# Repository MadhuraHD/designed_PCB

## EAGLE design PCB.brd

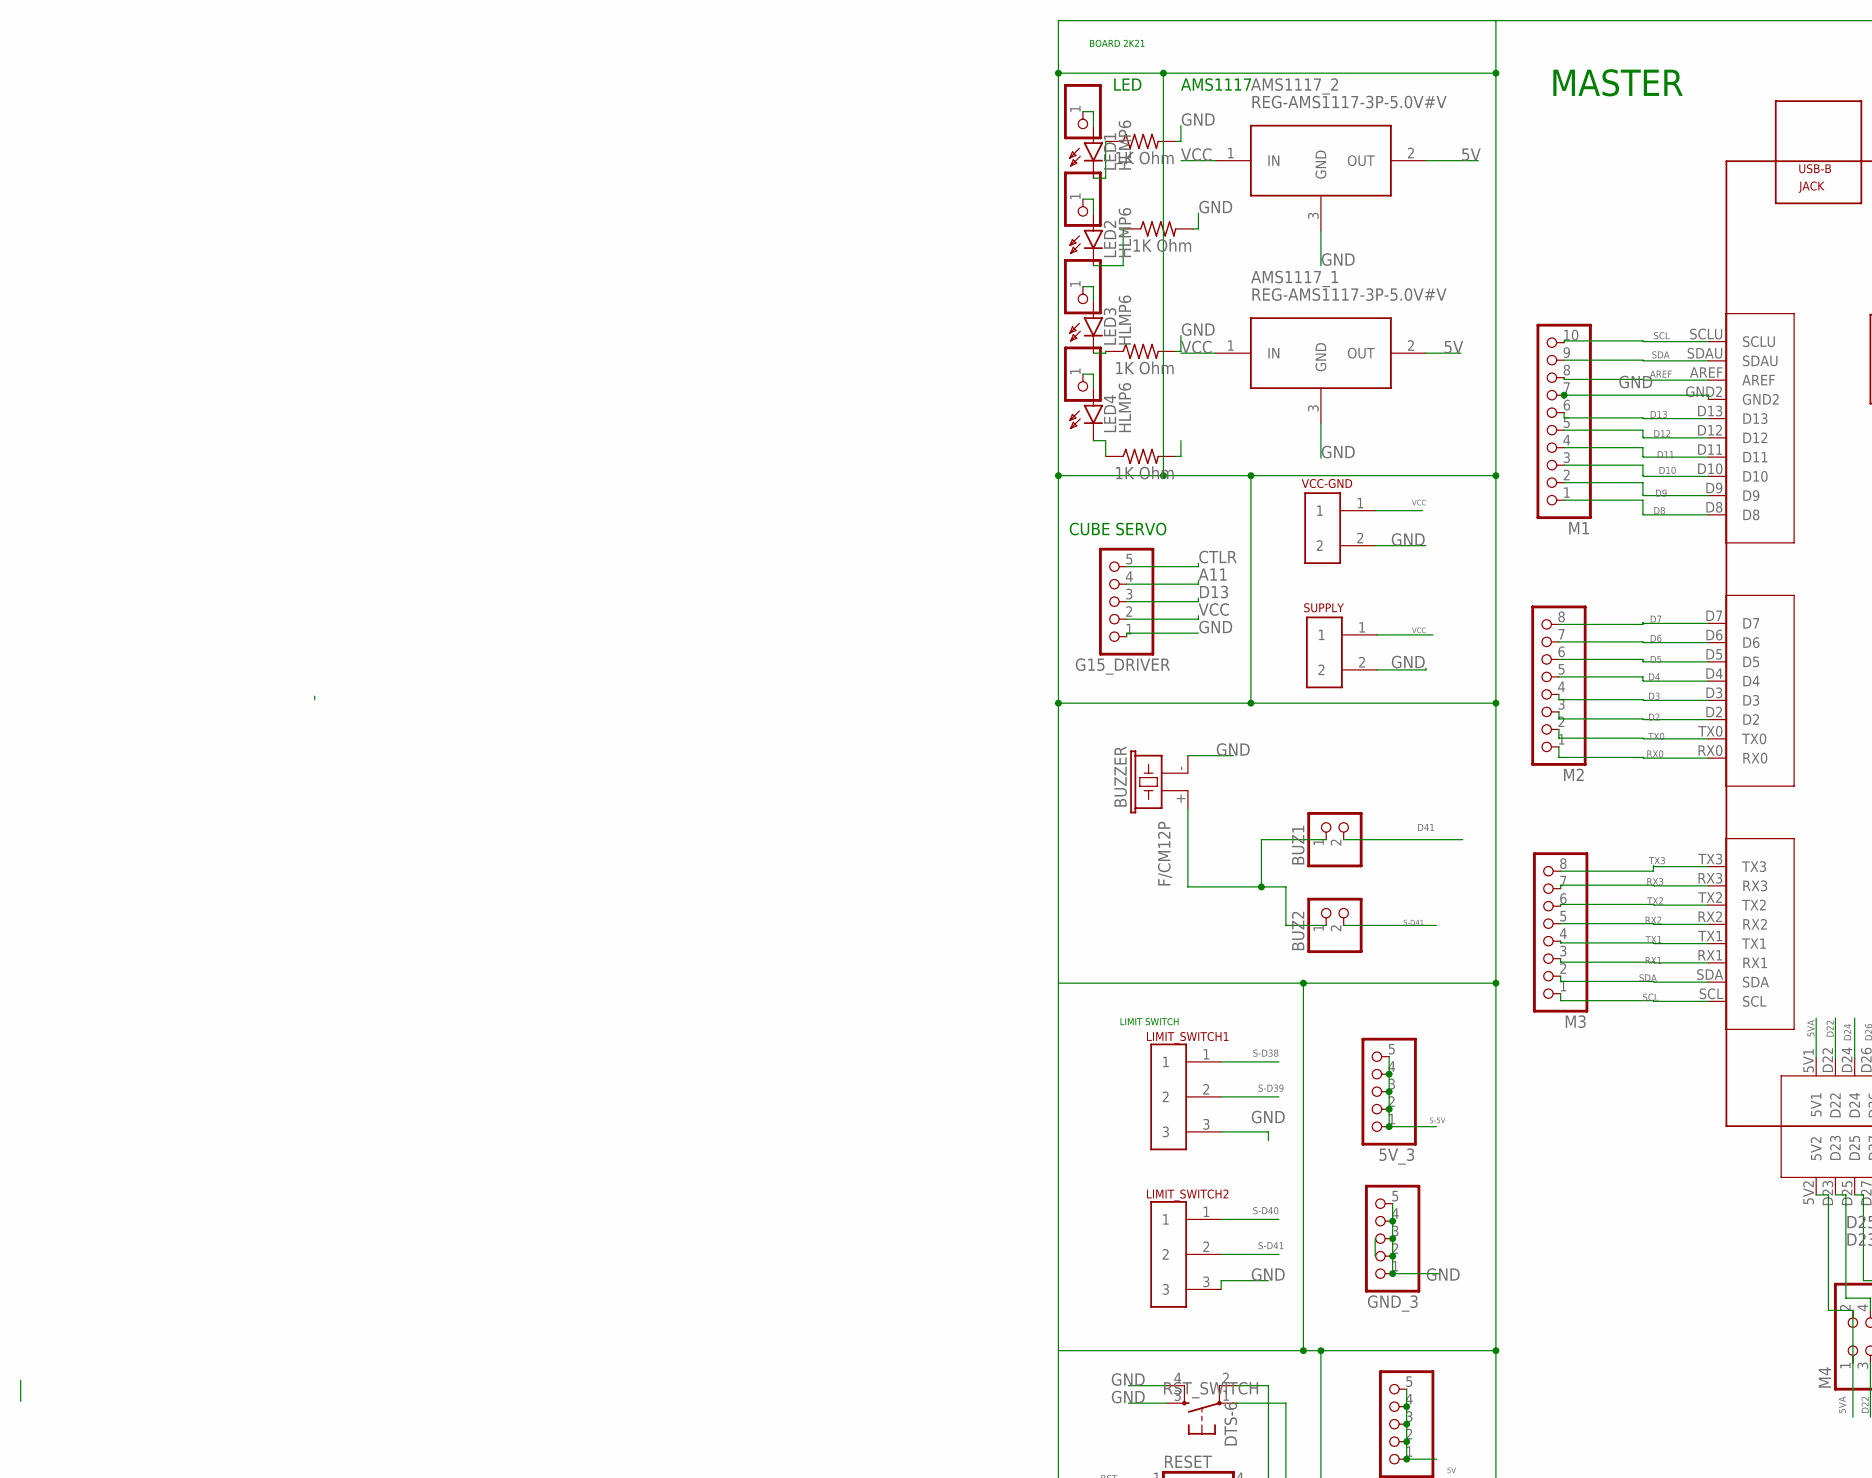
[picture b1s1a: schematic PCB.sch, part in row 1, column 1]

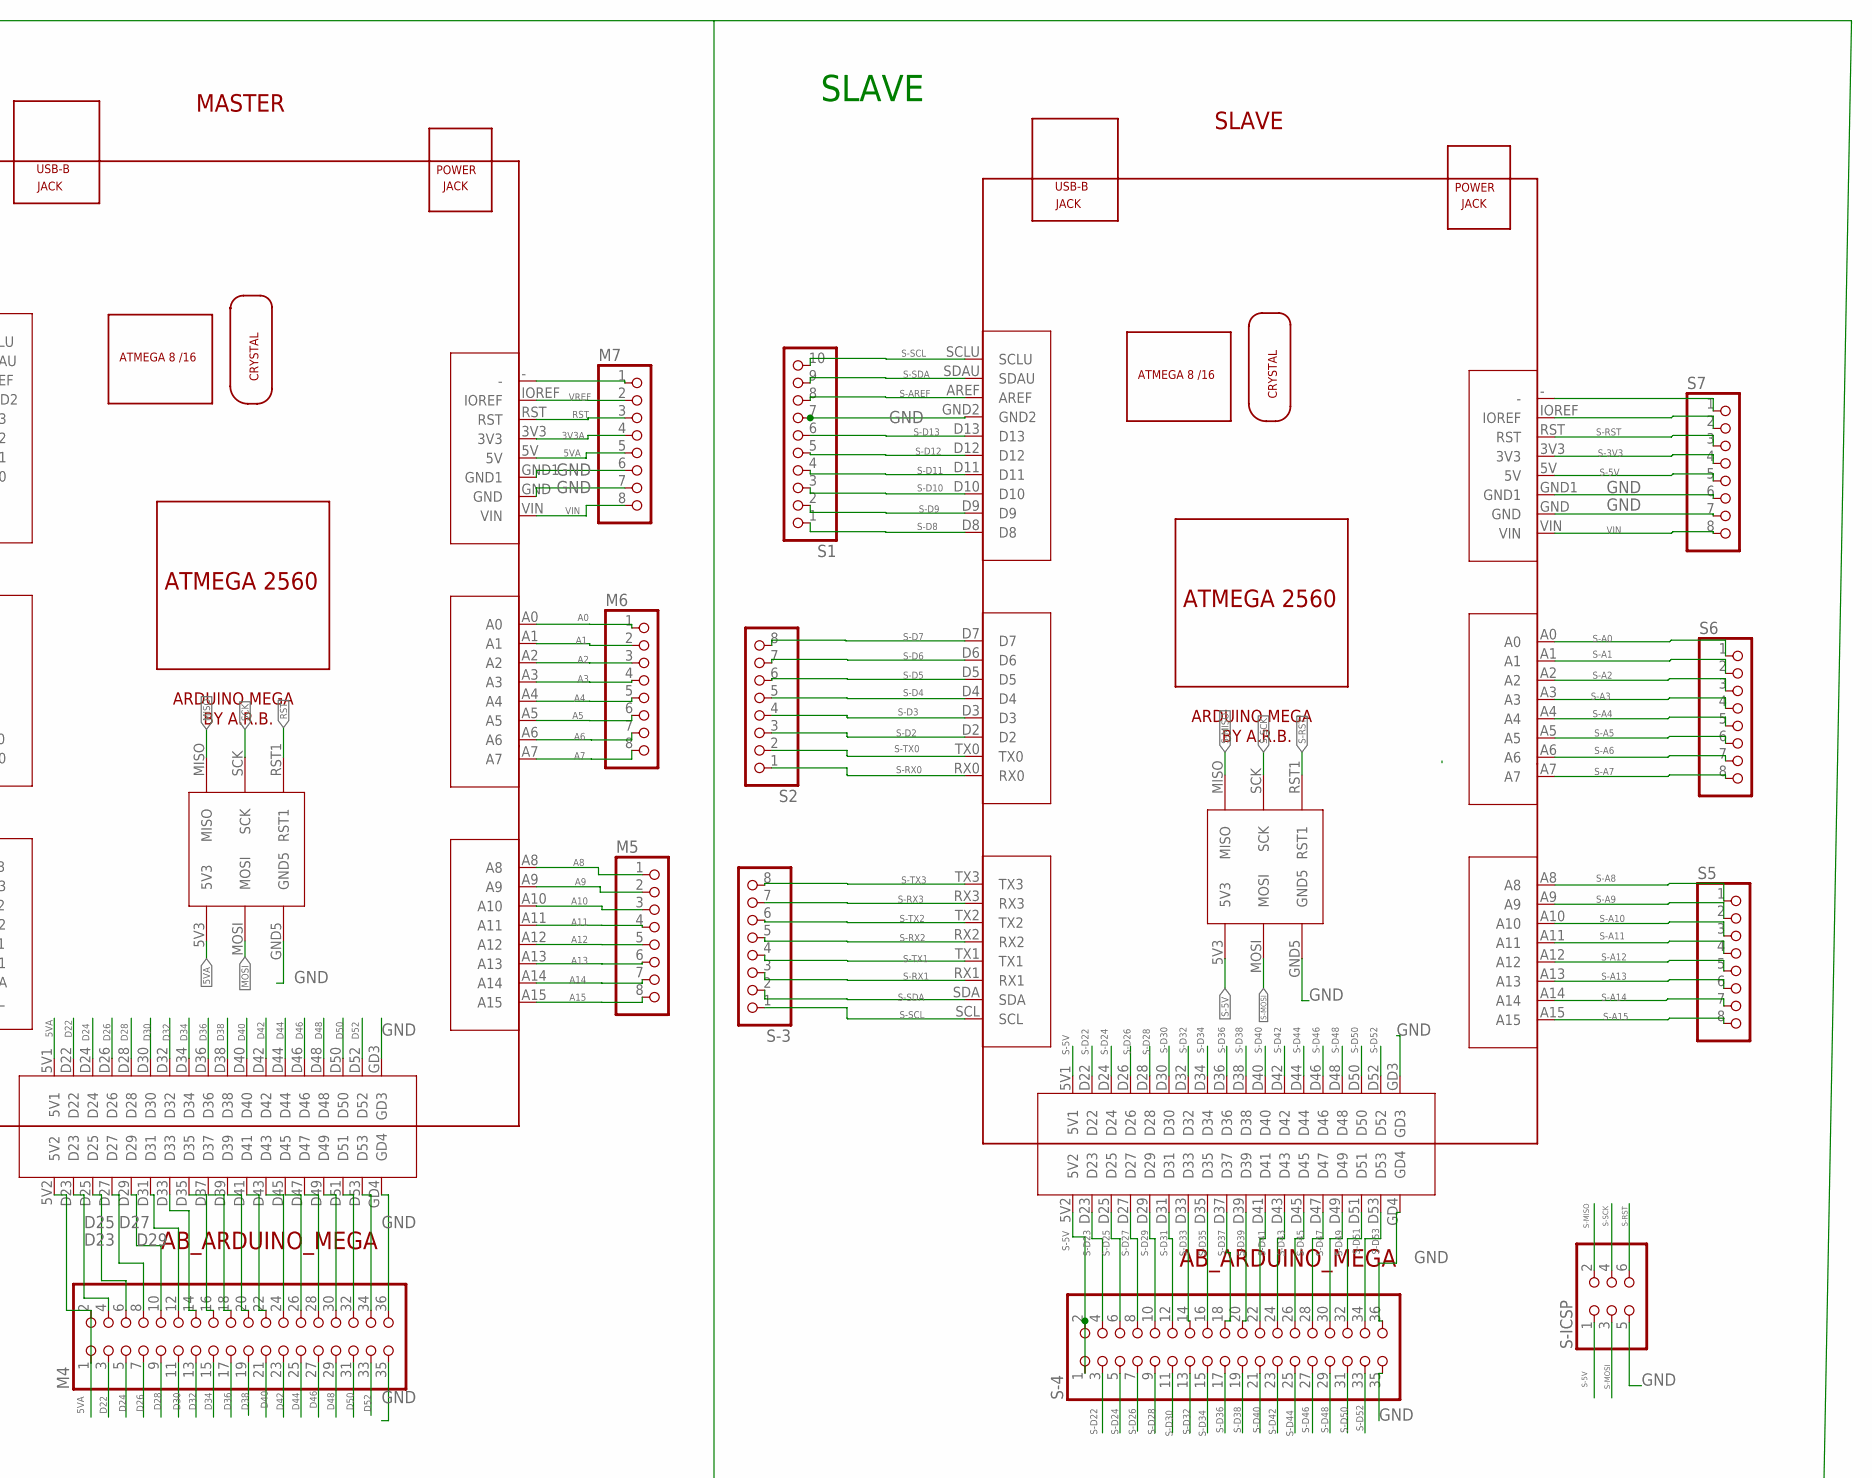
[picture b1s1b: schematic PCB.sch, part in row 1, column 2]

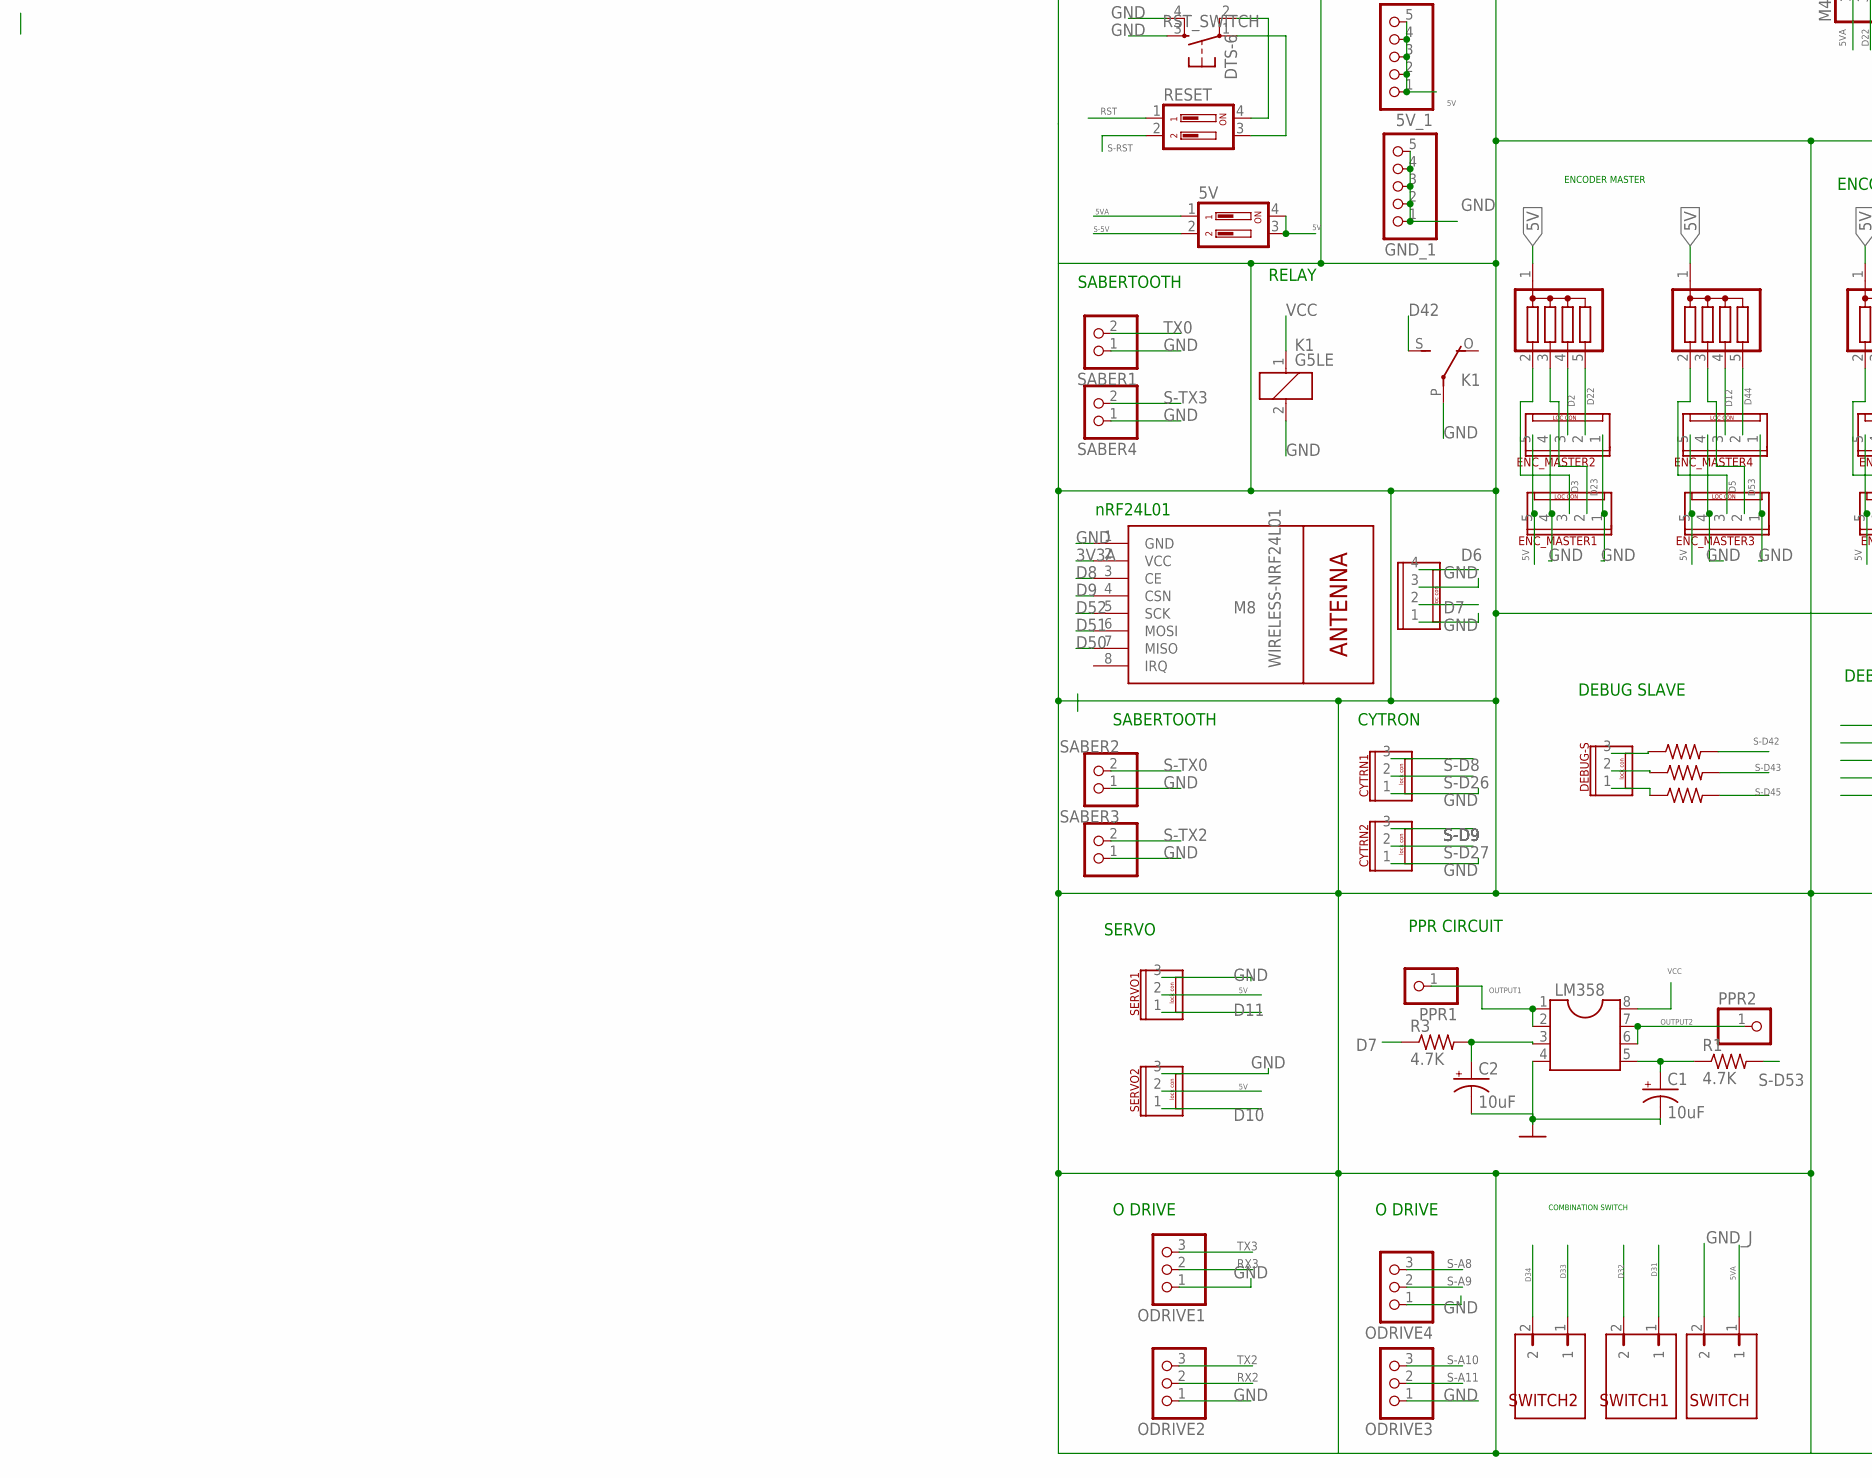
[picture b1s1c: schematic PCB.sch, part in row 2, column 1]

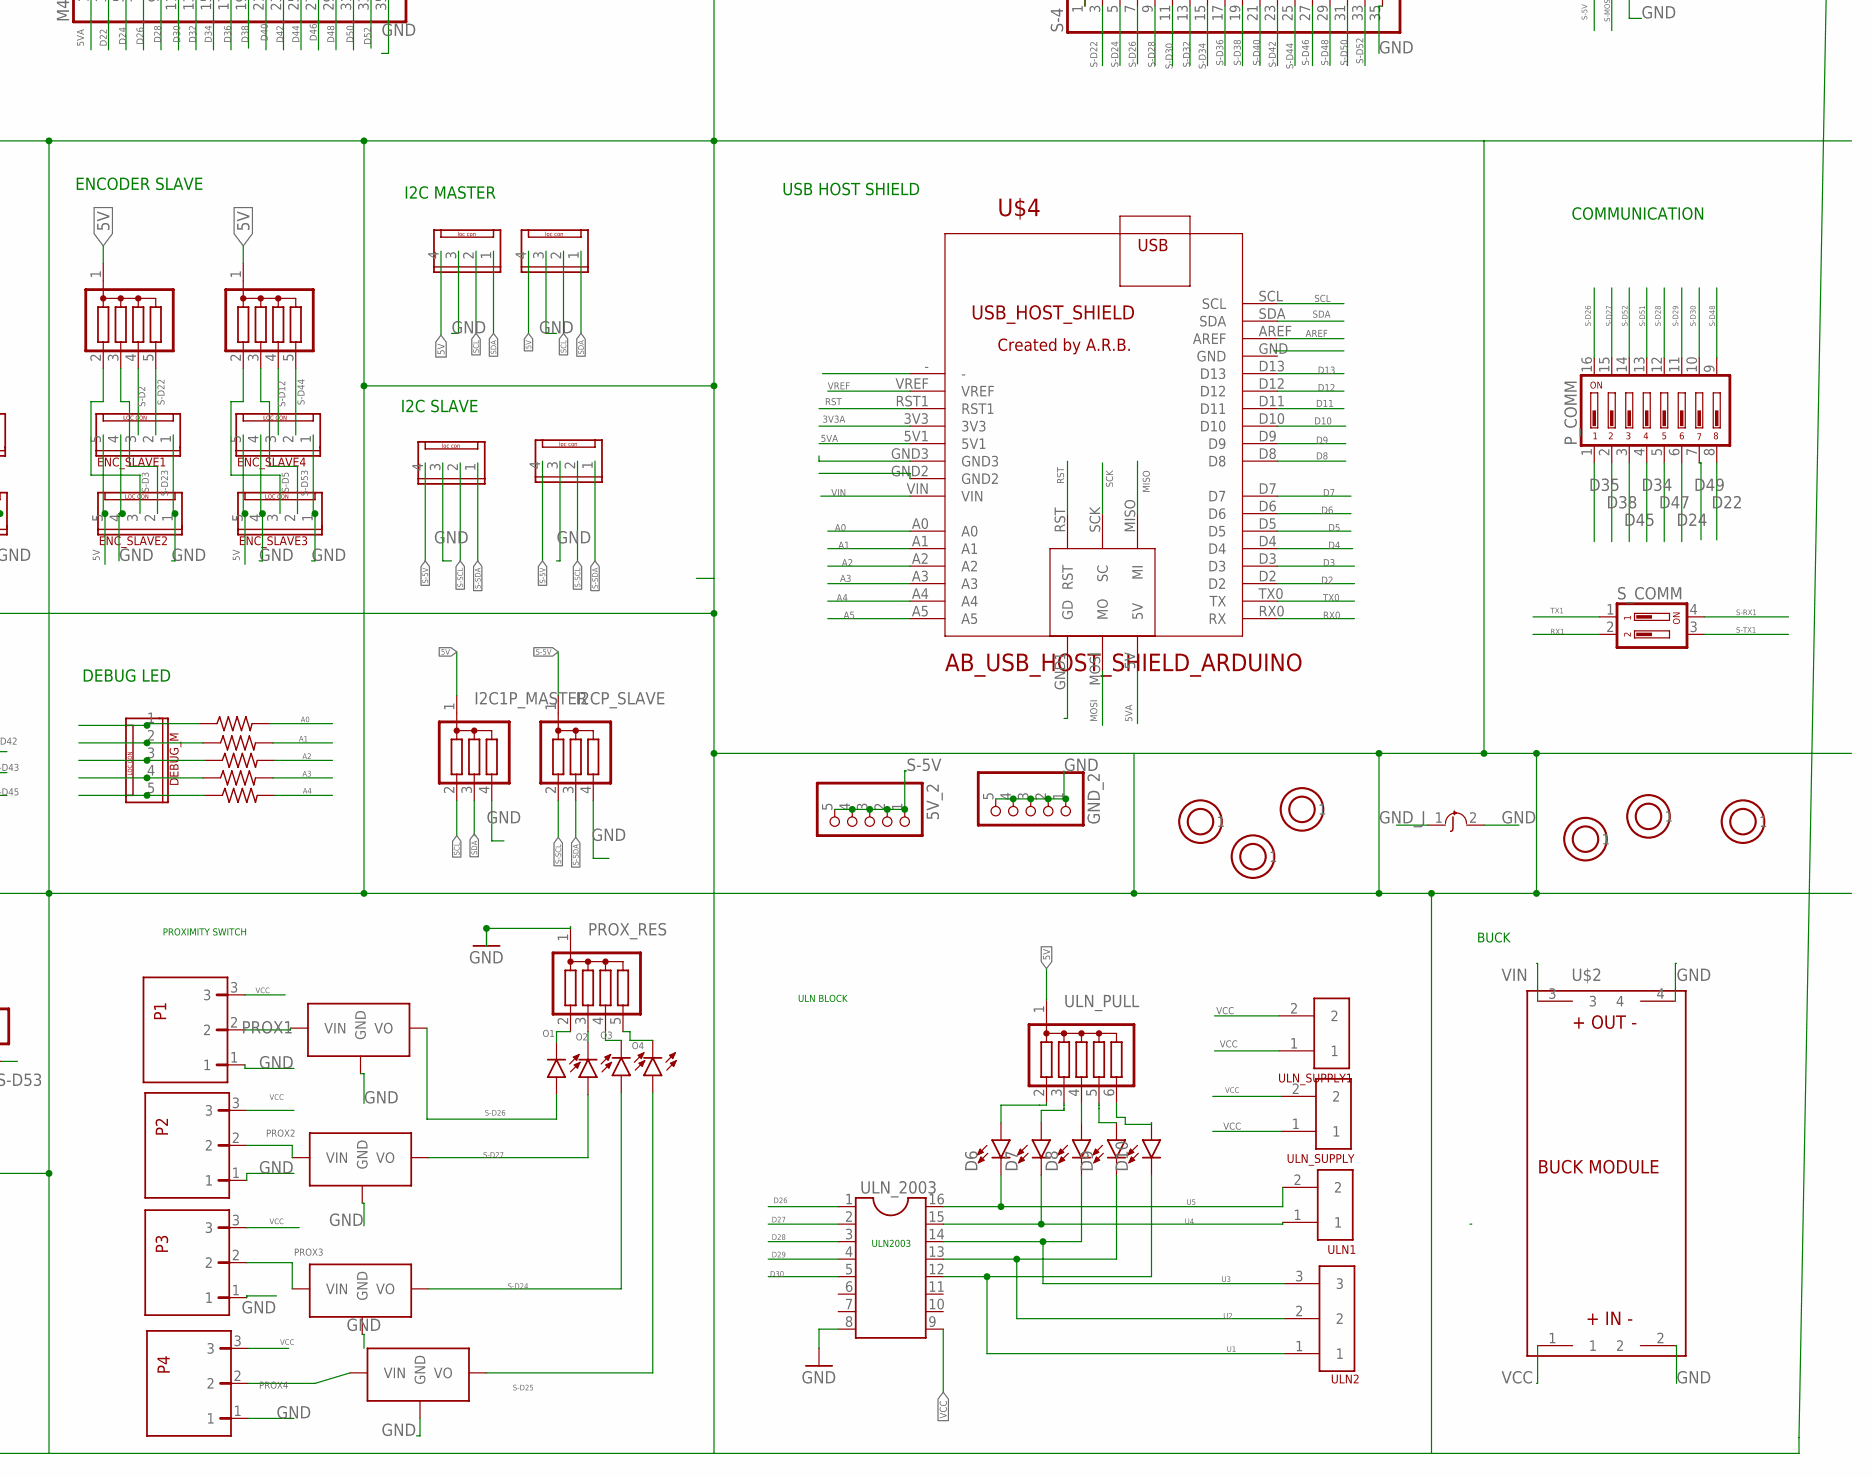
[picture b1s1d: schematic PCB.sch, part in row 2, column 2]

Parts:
5V: DIP02YL
5V_1, 5V_2, 5V_3: PINHD-1X5; 1X05
AMS1117_1, AMS1117_2: REG-AMS1117-3P-5.0V#V; REG-AMS1117-3P#V
BUZ1, BUZ2: PINHD-1X2; 1X02
BUZZER: F/CM12P
C1, C2: 10uF; CPOL-RADIAL-2.5MM-5MM
CYTRN1, CYTRN2: AB_3PIN_LOC_CONNECTOR
D1, D2, D3, D6, D7, D8, D9, D10, D14: LED-3MM-NO_SILK; LED_3MM-NS
DEBUG-S: AB_3PIN_LOC_CONNECTOR
DEBUG_M: AB_5PIN_LOC_CONNECTOR
ENC_MASTER1, ENC_MASTER2, ENC_MASTER3, ENC_MASTER4: AB_5PIN_LOC_CONNECTOR
ENC_SLAVE1, ENC_SLAVE2, ENC_SLAVE3, ENC_SLAVE4: AB_5PIN_LOC_CONNECTOR
G15_DRIVER: PINHD-1X5; 1X05
GND_1, GND_2, GND_3: PINHD-1X5; 1X05
I2C1P_MASTER, I2CP_SLAVE: G03R; SIL4
IMU_BLOCK2, IMU_BLOCK3, IMU_BLOCK4: AB_4PIN_LOC_CONNECTOR
IMU_MASTER: AB_4PIN_LOC_CONNECTOR
K1: G5LE
LED1, LED2, LED3, LED4: HLMP6
LIMIT_SWITCH1, LIMIT_SWITCH2: AB_SCREW_TER_5MM_3PIN
LM358: DIL8; DIL08
M1: PINHD-1X10; 1X10
M2, M3, M5, M6, M7: PINHD-1X8; 1X08
M4: PINHD-2X18; 2X18
M8: WIRELESS-NRF24L01
MASTER: AB_ARDUINO_MEGA
ODRIVE1, ODRIVE2, ODRIVE3, ODRIVE4: PINHD-1X3; 1X03
P1: P1; AB_RIGHT_TER_BLK_3PIN
P2: P2; AB_RIGHT_TER_BLK_3PIN
P3: P3; AB_RIGHT_TER_BLK_3PIN
P4: P4; AB_RIGHT_TER_BLK_3PIN
PPR1, PPR2, PPR5, PPR6, PPR7, PPR8: PINHD-1X1; 1X01
PROX_RES: G04R; SIL5
PULL_MASTER1, PULL_MASTER2: G04R; SIL5
PULL_SLAVE3: G04R; SIL5
P_COMM: DIP08YL
R1, R3: 4.7K; 0204/7
R2, R4, R5, R6, R7, R8, R9, R10: R-US_0204/7; 0204/7
R13, R14, R15, R16: 1K Ohm; 0204/7
RESET: DIP02YL
RST_SWITCH: DTS-6
S1: PINHD-1X10; 1X10
S2, S5, S6, S7: PINHD-1X8; 1X08
S-3: PINHD-1X8; 1X08
S-4: PINHD-2X18; 2X18
S-ICSP: PINHD-2X3; 2X03
SABER1, SABER2, SABER3, SABER4: PINHD-1X2; 1X02
SERVO1, SERVO2: AB_3PIN_LOC_CONNECTOR
SLAVE: AB_ARDUINO_MEGA
STEPPER: AB_4PIN_LOC_CONNECTOR
SUPPLY: AB_SCREW_TERMINAL_5MM_2PIN
SWITCH, SWITCH1, SWITCH2: AB_RIGHT_TER_BLK
S_COMM: DIP02YL
S_ENC_PULL1: G04R; SIL5
U$2: BUCK_MODULEWITH_SMDPADS&THROUGHHOLES; BUCK_MODULE
U$3, U$5, U$6, U$7, U$8, U$9: PLATED_DRILL_3.5MM
U$4: AB_USB_HOST_SHIELD_ARDUINO
U$23, U$24, U$25, U$26: AB_7805_FLAT
U$35: AB_JUMPER_ONE_WAY
ULN1: AB_SCREW_TERMINAL_5MM_2PIN
ULN2: AB_SCREW_TER_5MM_3PIN
ULN_2003: DIL16
ULN_PULL: G05R; SIL6
ULN_SUPPLY, ULN_SUPPLY1: AB_SCREW_TERMINAL_5MM_2PIN
VCC-GND: AB_SCREW_TERMINAL_5MM_2PIN

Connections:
3V3A: M7.4, M8.2 (VCC), MASTER.3V3, U$4.3V3
5V: 5V.3, 5V.4, 5V_1.1, 5V_1.2, 5V_1.3, 5V_1.4, 5V_1.5, AMS1117_1.2 (OUT), AMS1117_2.2 (OUT), ENC_MASTER1.5, ENC_MASTER2.5, ENC_MASTER3.5, ENC_MASTER4.5, ENC_SLAVE1.5, ENC_SLAVE2.5, ENC_SLAVE3.5, ENC_SLAVE4.5, I2C1P_MASTER.1, IMU_BLOCK2.4, IMU_MASTER.4, PULL_MASTER1.1, PULL_MASTER2.1, PULL_SLAVE3.1, SERVO1.2, SERVO2.2, S_ENC_PULL1.1, ULN_PULL.1
5VA: 5V.1, M4.1, M4.2, M7.5, MASTER.5V, MASTER.5V1, MASTER.5V2, MASTER.5V3, SWITCH.1, U$4.5V, U$4.5V1
A0: M6.1, MASTER.A0, R2.2, U$4.A0
A1: M6.2, MASTER.A1, R4.2, U$4.A1
A2: M6.3, MASTER.A2, R5.2, U$4.A2
A3: M6.4, MASTER.A3, R6.2, U$4.A3
A4: M6.5, MASTER.A4, R7.2, U$4.A4
A5: M6.6, MASTER.A5, U$4.A5
A6: M6.7, MASTER.A6
A7: M6.8, MASTER.A7
A8: M5.1, MASTER.A8
A9: M5.2, MASTER.A9
A10: M5.3, MASTER.A10
A11: G15_DRIVER.4, M5.4, MASTER.A11
A12: M5.5, MASTER.A12
A13: M5.6, MASTER.A13
A14: M5.7, MASTER.A14
A15: M5.8, MASTER.A15
AREF: M1.8, MASTER.AREF, U$4.AREF
CTLR: G15_DRIVER.5
D2: ENC_MASTER2.3, M2.3, MASTER.D2, PULL_MASTER1.4, U$4.D2
D3: ENC_MASTER1.3, M2.4, MASTER.D3, PULL_MASTER1.2, U$4.D3
D4: M2.5, MASTER.D4, U$4.D4
D5: ENC_MASTER3.3, M2.6, MASTER.D5, PULL_MASTER2.2, U$4.D5
D6: M2.7, MASTER.D6, STEPPER.4, U$4.D6
D7: M2.8, MASTER.D7, R3.1, STEPPER.2, U$4.D7
D8: M1.1, M8.3 (CE), MASTER.D8, U$4.D8
D9: M1.2, M8.4 (CSN), MASTER.D9, U$4.D9
D10: M1.3, MASTER.D10, SERVO2.1, U$4.D10
D11: M1.4, MASTER.D11, SERVO1.1, U$4.D11
D12: ENC_MASTER4.3, M1.5, MASTER.D12, PULL_MASTER2.4, U$4.D12
D13: G15_DRIVER.3, M1.6, MASTER.D13, U$4.D13
D22: ENC_MASTER2.2, M4.3, MASTER.D22, PULL_MASTER1.5, P_COMM.8
D23: ENC_MASTER1.2, M4.4, MASTER.D23, PULL_MASTER1.3
D24: M4.5, MASTER.D24, P_COMM.6
D25: M4.6, MASTER.D25
D26: M4.7, MASTER.D26, ULN_2003.1
D27: M4.8, MASTER.D27, ULN_2003.2
D28: M4.9, MASTER.D28, ULN_2003.3
D29: M4.10, MASTER.D29, ULN_2003.4
D30: M4.11, MASTER.D30, ULN_2003.5
D31: M4.12, MASTER.D31, SWITCH1.1
D32: M4.13, MASTER.D32, SWITCH1.2
D33: M4.14, MASTER.D33, SWITCH2.1
D34: M4.15, MASTER.D34, P_COMM.4, SWITCH2.2
D35: M4.16, MASTER.D35, P_COMM.1
D36: M4.17, MASTER.D36
D38: M4.19, MASTER.D38, P_COMM.2
D39: M4.18, MASTER.D37
D40: M4.21, MASTER.D40
D41: BUZ1.2, M4.20, MASTER.D39
D42: K1.S, M4.23, MASTER.D42
D43: M4.22, MASTER.D41
D44: ENC_MASTER4.2, M4.25, MASTER.D44, PULL_MASTER2.5
D45: M4.24, MASTER.D43, P_COMM.3
D46: M4.27, MASTER.D46
D47: M4.26, MASTER.D45, P_COMM.5
D48: M4.29, MASTER.D48
D49: M4.28, MASTER.D47, P_COMM.7
D50: M4.31, M8.7 (MISO), MASTER.D50
D51: M4.30, M8.6 (MOSI), MASTER.D49
D52: M4.33, M8.5 (SCK), MASTER.D52
D53: ENC_MASTER3.2, M4.32, MASTER.D51, PULL_MASTER2.3
D54: M4.34, MASTER.D53
GND: AMS1117_1.3 (GND), AMS1117_2.3 (GND), BUZZER.- (2), C1.2 (-), C2.2 (-), CYTRN1.1, CYTRN2.1, ENC_MASTER1.1, ENC_MASTER1.4, ENC_MASTER2.1, ENC_MASTER2.4, ENC_MASTER3.1, ENC_MASTER3.4, ENC_MASTER4.1, ENC_MASTER4.4, ENC_SLAVE1.1, ENC_SLAVE1.4, ENC_SLAVE2.1, ENC_SLAVE2.4, ENC_SLAVE3.1, ENC_SLAVE3.4, ENC_SLAVE4.1, ENC_SLAVE4.4, G15_DRIVER.1, GND_1.1, GND_1.2, GND_1.3, GND_1.4, GND_1.5, GND_2.1, GND_2.2, GND_2.3, GND_2.4, GND_2.5, GND_3.1, GND_3.2, GND_3.3, GND_3.4, GND_3.5, I2C1P_MASTER.4, I2CP_SLAVE.4, IMU_BLOCK2.3, IMU_BLOCK3.3, IMU_BLOCK4.3, IMU_MASTER.3, K1.2, K1.P, LIMIT_SWITCH1.3, LIMIT_SWITCH2.3, LM358.4, M1.7, M4.35, M4.36, M7.6, M7.7, M8.1 (GND), MASTER.GD3, MASTER.GD4, MASTER.GND, MASTER.GND1, MASTER.GND2, MASTER.GND5, ODRIVE1.1, ODRIVE2.1, ODRIVE3.1, ODRIVE4.1, P1.1, P2.1, P3.1, P4.1, PROX_RES.1, R13.2, R14.2, R15.2, RST_SWITCH.3, RST_SWITCH.4, S1.7, S7.6, S7.7, S-4.35, S-4.36, S-ICSP.5, SABER1.1, SABER2.1, SABER3.1, SABER4.1, SERVO1.3, SERVO2.3, SLAVE.GD3, SLAVE.GD4, SLAVE.GND, SLAVE.GND1, SLAVE.GND2, SLAVE.GND5, STEPPER.1, STEPPER.3, SUPPLY.2, U$2.2, U$2.4, U$23.2 (GND), U$24.2 (GND), U$25.2 (GND), U$26.2 (GND), U$35.2, ULN_2003.8, VCC-GND.2
GND_J: SWITCH.2, U$35.1
MISO: MASTER.MISO, U$4.MISO (MI)
MOSI: MASTER.MOSI, U$4.MOSI (MO)
unnamed: C1.1 (+), LM358.5, R1.1
unnamed: M7.1, MASTER.-
unnamed: S7.1, SLAVE.-
unnamed: BUZ1.1, BUZ2.1, BUZZER.+ (1)
unnamed: C2.1 (+), LM358.3, R3.2
unnamed: DEBUG_M.1, R2.1
unnamed: D6.A, ULN_PULL.2
unnamed: D7.A, ULN_PULL.3
unnamed: D8.A, ULN_PULL.4
unnamed: D9.A, ULN_PULL.5
unnamed: D10.A, ULN_PULL.6
unnamed: RESET.4, RST_SWITCH.2
unnamed: RESET.3, RST_SWITCH.1
unnamed: DEBUG_M.2, R4.1
unnamed: DEBUG_M.3, R5.1
unnamed: DEBUG_M.4, R6.1
unnamed: DEBUG_M.5, R7.1
unnamed: LED1.A, PPR5.1
unnamed: LED2.A, PPR6.1
unnamed: DEBUG-S.3, R8.1
unnamed: DEBUG-S.2, R9.1
unnamed: DEBUG-S.1, R10.1
unnamed: LED3.A, PPR7.1
unnamed: LED4.A, PPR8.1
unnamed: LED4.K, R16.1
unnamed: LED3.K, R15.1
unnamed: LED2.K, R14.1
unnamed: LED1.K, R13.1
unnamed: S7.2, SLAVE.IOREF
O1: D14.K (C), PROX_RES.2
O2: D1.K (C), PROX_RES.3
O3: D2.K (C), PROX_RES.4
O4: D3.K (C), PROX_RES.5
OUTPUT1: LM358.1, LM358.2, PPR1.1
OUTPUT2: LM358.6, LM358.7, PPR2.1
PROX1: P1.2, U$23.1 (VIN)
PROX2: P2.2, U$24.1 (VIN)
PROX3: P3.2, U$25.1 (VIN)
PROX4: P4.2, U$26.1 (VIN)
RST: M7.3, MASTER.RST, MASTER.RST1, RESET.1, U$4.RST, U$4.RST1
RX0: M2.1, MASTER.RX0, U$4.RX0 (RX)
RX1: M3.3, MASTER.RX1, S_COMM.2
RX2: M3.5, MASTER.RX2, ODRIVE2.2
RX3: M3.7, MASTER.RX3, ODRIVE1.2
S-3V3: S7.4, SLAVE.3V3
S-5V: 5V.2, 5V_2.1, 5V_2.2, 5V_2.3, 5V_2.4, 5V_2.5, 5V_3.1, 5V_3.2, 5V_3.3, 5V_3.4, 5V_3.5, I2CP_SLAVE.1, IMU_BLOCK3.4, IMU_BLOCK4.4, S7.5, S-4.1, S-4.2, S-ICSP.1, SLAVE.5V, SLAVE.5V1, SLAVE.5V2, SLAVE.5V3
S-A0: S6.1, SLAVE.A0
S-A1: S6.2, SLAVE.A1
S-A2: S6.3, SLAVE.A2
S-A3: S6.4, SLAVE.A3
S-A4: S6.5, SLAVE.A4
S-A5: S6.6, SLAVE.A5
S-A6: S6.7, SLAVE.A6
S-A7: S6.8, SLAVE.A7
S-A8: ODRIVE4.3, S5.1, SLAVE.A8
S-A9: ODRIVE4.2, S5.2, SLAVE.A9
S-A10: ODRIVE3.3, S5.3, SLAVE.A10
S-A11: ODRIVE3.2, S5.4, SLAVE.A11
S-A12: S5.5, SLAVE.A12
S-A13: S5.6, SLAVE.A13
S-A14: S5.7, SLAVE.A14
S-A15: S5.8, SLAVE.A15
S-AREF: S1.8, SLAVE.AREF
S-D2: ENC_SLAVE1.3, S2.3, SLAVE.D2, S_ENC_PULL1.4
S-D3: ENC_SLAVE2.3, S2.4, SLAVE.D3, S_ENC_PULL1.2
S-D4: S2.5, SLAVE.D4
S-D5: ENC_SLAVE3.3, PULL_SLAVE3.2, S2.6, SLAVE.D5
S-D6: S2.7, SLAVE.D6
S-D7: S2.8, SLAVE.D7
S-D8: CYTRN1.3, S1.1, SLAVE.D8
S-D9: CYTRN2.3, S1.2, SLAVE.D9
S-D10: S1.3, SLAVE.D10
S-D11: S1.4, SLAVE.D11
S-D12: ENC_SLAVE4.3, PULL_SLAVE3.4, S1.5, SLAVE.D12
S-D13: S1.6, SLAVE.D13
S-D22: ENC_SLAVE1.2, S-4.3, SLAVE.D22, S_ENC_PULL1.5
S-D23: ENC_SLAVE2.2, S-4.4, SLAVE.D23, S_ENC_PULL1.3
S-D24: D2.A, S-4.5, SLAVE.D24, U$25.3 (VO)
S-D25: D3.A, S-4.6, SLAVE.D25, U$26.3 (VO)
S-D26: CYTRN1.2, D14.A, P_COMM.16, S-4.7, SLAVE.D26, U$23.3 (VO)
S-D27: CYTRN2.2, D1.A, P_COMM.15, S-4.8, SLAVE.D27, U$24.3 (VO)
S-D28: P_COMM.12, S-4.9, SLAVE.D28
S-D29: P_COMM.11, S-4.10, SLAVE.D29
S-D30: P_COMM.10, S-4.11, SLAVE.D30
S-D31: S-4.12, SLAVE.D31
S-D32: S-4.13, SLAVE.D32
S-D33: S-4.14, SLAVE.D33
S-D34: S-4.15, SLAVE.D34
S-D35: S-4.16, SLAVE.D35
S-D36: S-4.17, SLAVE.D36
S-D37: S-4.18, SLAVE.D37
S-D38: LIMIT_SWITCH1.1, S-4.19, SLAVE.D38
S-D39: LIMIT_SWITCH1.2, S-4.20, SLAVE.D39
S-D40: LIMIT_SWITCH2.1, S-4.21, SLAVE.D40
S-D41: BUZ2.2, LIMIT_SWITCH2.2, S-4.22, SLAVE.D41
S-D42: R8.2, S-4.23, SLAVE.D42
S-D43: R9.2, S-4.24, SLAVE.D43
S-D44: ENC_SLAVE4.2, PULL_SLAVE3.5, S-4.25, SLAVE.D44
S-D45: R10.2, S-4.26, SLAVE.D45
S-D46: S-4.27, SLAVE.D46
S-D47: S-4.28, SLAVE.D47
S-D48: P_COMM.9, S-4.29, SLAVE.D48
S-D49: S-4.30, SLAVE.D49
S-D50: S-4.31, SLAVE.D50
S-D51: P_COMM.13, S-4.32, SLAVE.D51
S-D52: P_COMM.14, S-4.33, SLAVE.D52
S-D53: ENC_SLAVE3.2, PULL_SLAVE3.3, R1.2, S-4.34, SLAVE.D53
S-MISO: S-ICSP.2, SLAVE.MISO
S-MOSI: S-ICSP.3, SLAVE.MOSI
S-RST: RESET.2, S7.3, S-ICSP.6, SLAVE.RST, SLAVE.RST1
S-RX0: S2.1, SLAVE.RX0
S-RX1: S-3.3, SLAVE.RX1, S_COMM.4
S-RX2: S-3.5, SLAVE.RX2
S-RX3: S-3.7, SLAVE.RX3
S-SCK: S-ICSP.4, SLAVE.SCK
S-SCL: I2CP_SLAVE.2, IMU_BLOCK3.2, IMU_BLOCK4.2, S1.10, S-3.1, SLAVE.SCL, SLAVE.SCLU
S-SDA: I2CP_SLAVE.3, IMU_BLOCK3.1, IMU_BLOCK4.1, S1.9, S-3.2, SLAVE.SDA, SLAVE.SDAU
S-TX0: S2.2, SABER2.2, SLAVE.TX0
S-TX1: S-3.4, SLAVE.TX1, S_COMM.3
S-TX2: S-3.6, SABER3.2, SLAVE.TX2
S-TX3: S-3.8, SABER4.2, SLAVE.TX3
SCK: MASTER.SCK, U$4.SCK (SC)
SCL: I2C1P_MASTER.2, IMU_BLOCK2.2, IMU_MASTER.2, M1.10, M3.1, MASTER.SCL, MASTER.SCLU, U$4.SCL
SDA: I2C1P_MASTER.3, IMU_BLOCK2.1, IMU_MASTER.1, M1.9, M3.2, MASTER.SDA, MASTER.SDAU, U$4.SDA
TX0: M2.2, MASTER.TX0, SABER1.2, U$4.TX0 (TX)
TX1: M3.4, MASTER.TX1, S_COMM.1
TX2: M3.6, MASTER.TX2, ODRIVE2.3
TX3: M3.8, MASTER.TX3, ODRIVE1.3
U1: D10.K (C), ULN2.1, ULN_2003.12
U2: D9.K (C), ULN2.2, ULN_2003.13
U3: D8.K (C), ULN2.3, ULN_2003.14
U4: D7.K (C), ULN1.1, ULN_2003.15
U5: D6.K (C), ULN1.2, ULN_2003.16
VCC: AMS1117_1.1 (IN), AMS1117_2.1 (IN), G15_DRIVER.2, K1.1, LM358.8, P1.3, P2.3, P3.3, P4.3, SUPPLY.1, U$2.1, ULN_2003.9, ULN_SUPPLY.1, ULN_SUPPLY.2, ULN_SUPPLY1.1, ULN_SUPPLY1.2, VCC-GND.1
VIN: M7.8, MASTER.VIN, S7.8, SLAVE.VIN, U$2.3, U$4.VIN
VREF: M7.2, MASTER.IOREF, U$4.VREF

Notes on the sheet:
BOARD 2K21
MASTER
SLAVE
USB HOST SHIELD
COMMUNICATION
I2C MASTER
ENCODER SLAVE
ENCODER MASTER
DEBUG SLAVE
DEBUG LED
I2C SLAVE
LIMIT SWITCH
PROXIMITY SWITCH
ULN2003
ULN BLOCK
BUCK
COMBINATION SWITCH
PPR CIRCUIT
CUBE SERVO
SERVO
O DRIVE
nRF24L01
CYTRON
SABERTOOTH
LED
RELAY
AMS1117

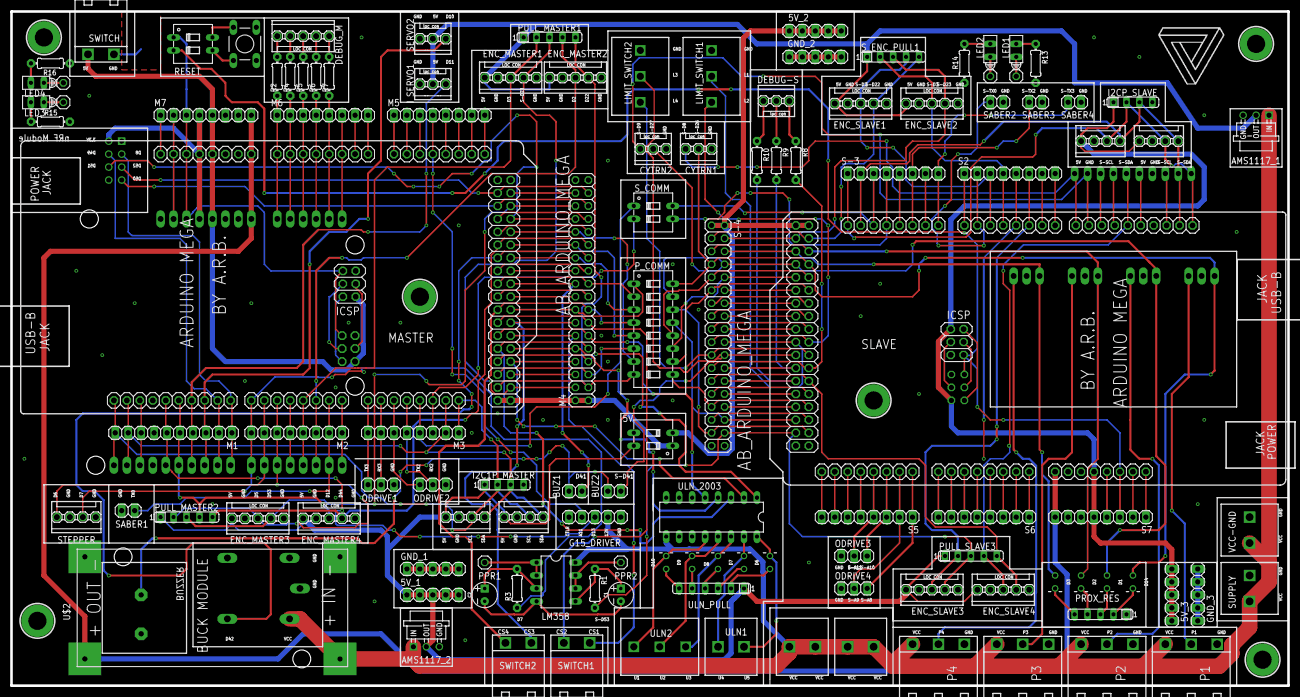
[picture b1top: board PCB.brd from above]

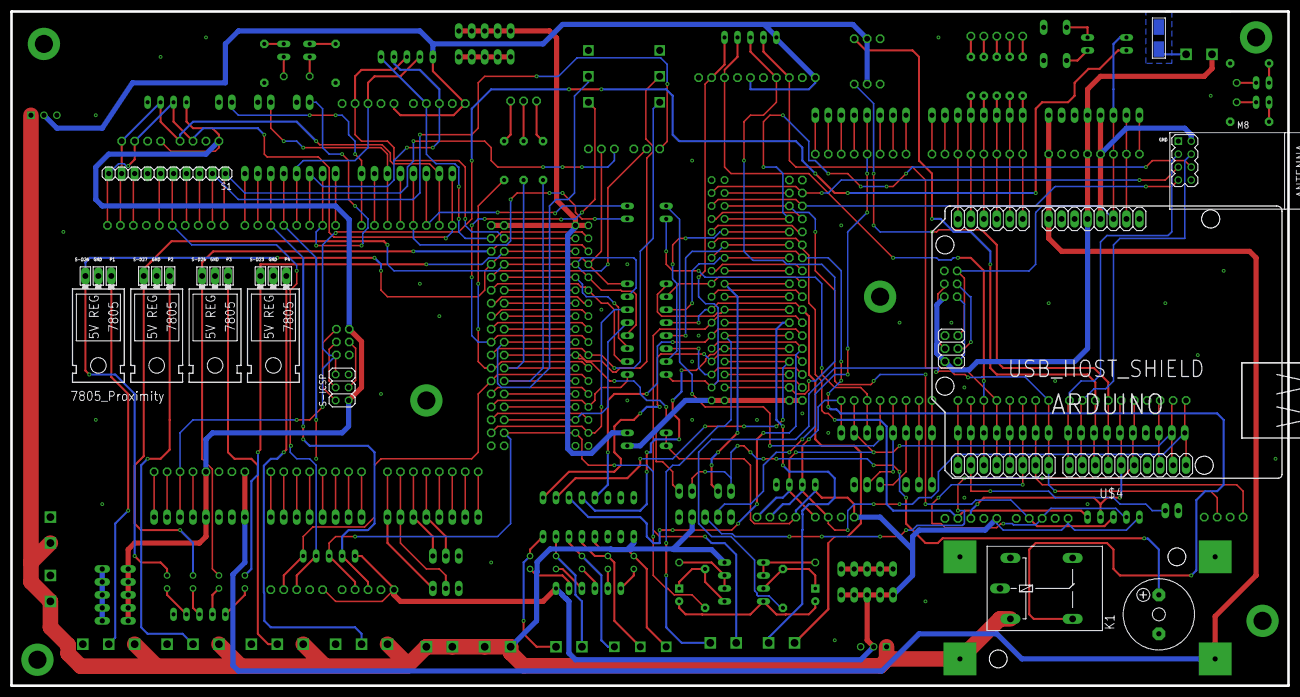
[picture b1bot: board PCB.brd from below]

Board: 2 copper layers, 250.2 x 132.1 mm, 136 parts (11 on the bottom side), 204 nets.

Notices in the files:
parts and their libraries:
SparkFun-Capacitors: Licensing: Creative Commons ShareAlike 4.0 International - https://creativecommons.org/licenses/by-sa/4.0
diy-modules: Released under the Creative Commons Attribution 4.0 International License: http://creativecommons.org/licenses/by/4.0
